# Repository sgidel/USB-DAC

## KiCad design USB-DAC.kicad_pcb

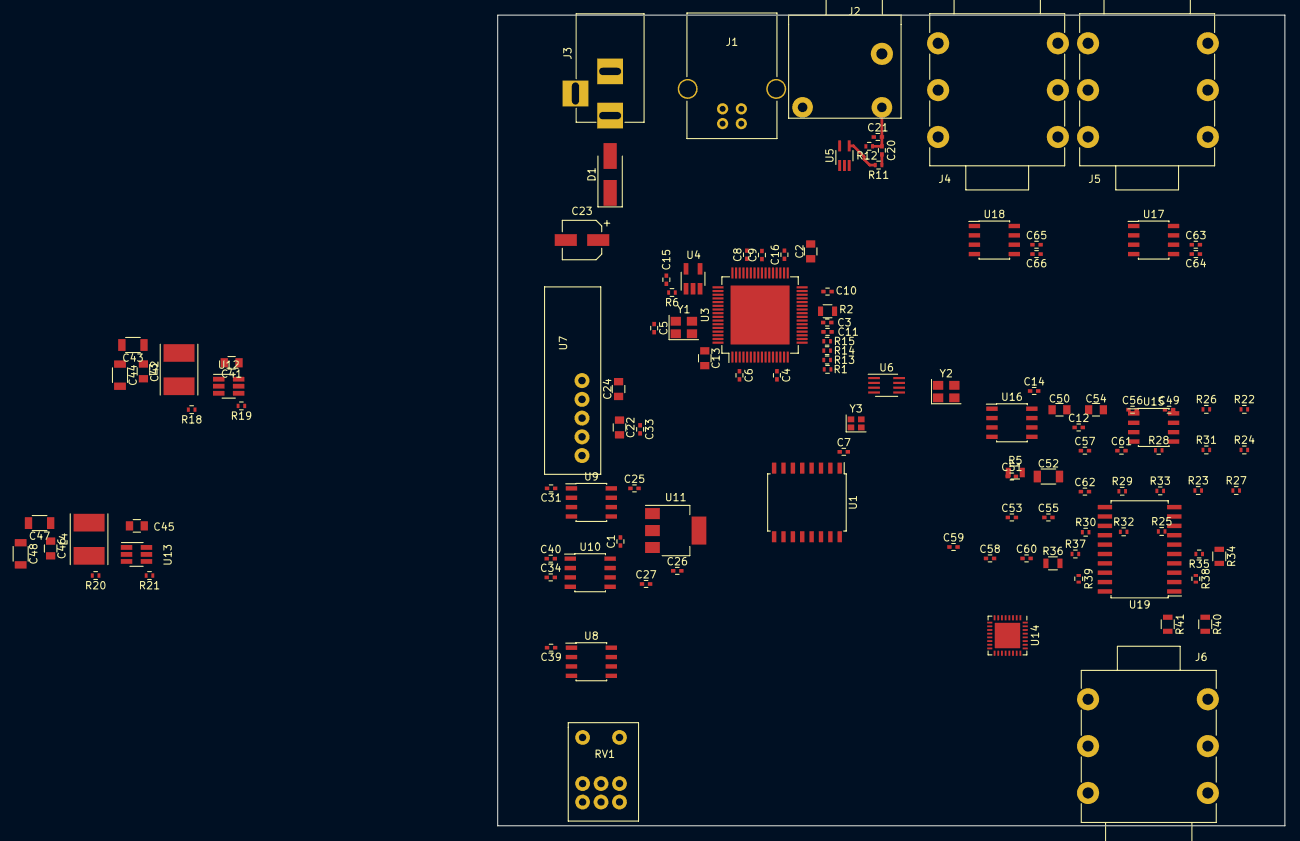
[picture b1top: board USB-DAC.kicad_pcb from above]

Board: 2 copper layers, 106.7 x 109.9 mm, 119 parts (0 on the bottom side), 75 nets.

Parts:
C1, C3, C4, C5, C6, C7, C8, C9, C10, C11, C12, C14, C15, C16, C20, C25, C26, C27, C31, C33, C34, C39, C40, C49, C51, C53, C63, C64, C65, C66: 100n; C_0402
C2, C13, C50: 10u; C_0805
C21: 100p; C_0402
C22, C24: 22u; C_0805
C23: 1000u; CP_Elec_5x5.7
C41, C42, C45, C46: 100n; C_0805
C43, C44, C47, C48: 47u; C_1206
C52: 10u; C_1206
C54: 1u; C_0805
C55, C56: 3n9; C_0402
C57, C58, C59, C60: 470p; C_0402
C61, C62: 22p; C_0402
D1: SK34ATR; D_SMA_Handsoldering
J1: USB_B
J2: SPDIF OUT; pjras1x1s_series
J3: BARREL_JACK
J4, J5, J6: Audio-Jack-3_3Switches; NMJ6HCD2
L3, L4: 2u2; L_Taiyo-Yuden_NR-50xx_HandSoldering
R1, R13, R14, R15: 0; R_0402
R2: 43.2; R_0805
R5: 4.7; R_0805
R6, R35, R37, R38, R39: 1K; R_0402
R11, R12: 220; R_0402
R18: 33K2; R_0402
R19: 10K2; R_0402
R20: 3K74; R_0402
R21: 10K; R_0402
R22, R23, R24, R25: 3K9; R_0402
R26, R27, R32, R33: 4K7; R_0402
R28, R29, R30, R31: 150; R_0402
R34, R36: 51; R_0805
R40, R41: 39.2; R_0805
RV1: P10K; PTR90
U1: ISO7340FC; SOIC-16W_7.5x10.3mm_Pitch1.27mm
U3: XHRA-2HPA; TQFP-64-1EP_10x10mm_Pitch0.5mm
U4: NCP303LSN09T1G; SOT-23-5_HandSoldering
U5: 74LVC1G79; SOT-353_SC-70-5_Handsoldering
U6: TC7WH157; SSOP-8_2.95x2.8mm_Pitch0.65mm
U7: CHINADCDC; chinadcdc
U8: LM78L12_SO8; SOIC-8_3.9x4.9mm_Pitch1.27mm
U9: L78L05_SO8; SOIC-8_3.9x4.9mm_Pitch1.27mm
U10: L79L12_SO8; SOIC-8_3.9x4.9mm_Pitch1.27mm
U11: AP1117-33; SOT-223-3_TabPin2
U12, U13: TPS563209; SOT-23-6_Handsoldering
U14: AK4452; QFN-32-1EP_5x5mm_Pitch0.5mm
U15, U16: NE5534; SOIC-8_3.9x4.9mm_Pitch1.27mm
U17, U18: DRV135; SOIC-8_3.9x4.9mm_Pitch1.27mm
U19: TPA6120A2; SOIC-20W_7.5x12.8mm_Pitch1.27mm
Y1: 24; Crystal_SMD_3225-4pin_3.2x2.5mm
Y2: 24.576; Crystal_SMD_3225-4pin_3.2x2.5mm
Y3: 22.5792; Crystal_SMD_2016-4pin_2.0x1.6mm

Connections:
+1V0: C9.1, C10.1, C11.1, C12.1, C13.1, C46.1, C47.1, C48.1, L4.2, R5.2, R20.2, U3.9, U3.10, U3.20, U3.27, U3.31, U3.39, U3.40, U3.41, U3.52, U3.56, U3.59, U4.2
+3.3VA: C27.1, C49.1, C50.1, U1.10, U1.16, U11.2, U14.11, U14.12, U14.13, U14.28, U14.29
+3V3: C1.1, C2.1, C3.1, C4.1, C5.1, C6.1, C7.1, C8.1, C16.1, C23.1, C25.1, C26.1, C42.1, C43.1, C44.1, D1.1, L3.2, R1.2, R6.2, R13.2, R14.2, R15.2, R18.2, U1.1, U3.3, U3.13, U3.22, U3.34, U3.44, U3.55, U5.5, U6.8, U7.1, U9.8, U11.3, U13.5, Y1.4, Y2.4, Y3.4
+5V: C31.1, C51.1, C52.1, C53.1, U9.1, U14.17, U14.21
+12V: C39.1, C63.1, C65.1, U8.1, U15.7, U16.7, U17.6, U18.6, U19.3, U19.18
-12V: C40.2, C64.2, C66.2, U10.1, U15.4, U16.4, U17.5, U18.5, U19.1, U19.20
/AK4452DAC/DIN: U1.12, U14.4
/AK4452DAC/LRCK: U1.13, U14.3
/AK4452DAC/MCLK: U1.14, U14.1
/AK4452DAC/OUTL: C59.1, R32.2, RV1.3, U15.6
/AK4452DAC/OUTR: C60.1, R33.2, RV1.6, U16.6
/Balanced Out/INL: R36.1, RV1.2, U17.4
/Balanced Out/INR: R34.1, RV1.5, U18.4
/USB/BCLK: U1.11, U14.2
/USB/CSEL: U3.38, U6.6
/USB/D+: J1.3, U3.25
/USB/D-: J1.2, U3.26
/USB/MCLK_INT: U1.3, U3.64, U5.2, U6.5
/USB/SPDIF: U3.42, U5.1
/USB/~RST: R6.1, U3.57, U4.1
GND: C1.2, C2.2, C3.2, C4.2, C5.2, C6.2, C7.2, C8.2, C9.2, C10.2, C11.2, C12.2, C13.2, C14.2, C15.2, C16.2, C21.1, C22.2, C23.2, C24.1, C25.2, C26.2, C27.2, C31.2, C33.2, C34.1, C39.2, C40.1, C42.2, C43.2, C44.2, C46.2, C47.2, C48.2, C49.2, C50.2, C51.2, C52.2, C53.2, C54.1, C57.2, C58.2, C63.2, C64.1, C65.2, C66.1, J1.4, J1.5, J2.2, J3.2, J3.3, J4.3, J4.6, J5.3, J5.6, J6.2, J6.5, R2.2, R12.1, R19.1, R21.1, R26.2, R27.2, R35.1, R37.1, RV1.1, RV1.4, U1.2, U1.8, U1.9, U1.15, U3.54, U3.65, U4.3, U5.3, U6.7, U7.2, U7.4, U8.2, U8.3, U8.6, U8.7, U9.2, U9.3, U9.6, U9.7, U10.5, U11.1, U12.1, U13.1, U14.5, U14.8, U14.9, U14.10, U14.16, U14.20, U14.22, U14.23, U14.24, U14.26, U14.27, U14.30, U17.3, U18.3, Y1.2, Y2.2, Y3.2
unnamed: C14.1, R5.1, U3.53
unnamed: C15.1, U4.5
unnamed: C20.1, C21.2, J2.1, R12.2
unnamed: C20.2, R11.1
unnamed: C22.1, C33.1, U7.3, U8.8
unnamed: C24.2, C34.2, U7.5, U10.2, U10.3, U10.6, U10.7
unnamed: C41.1, U12.6
unnamed: C41.2, L3.1, U12.2
unnamed: C45.1, U13.6
unnamed: C45.2, L4.1, U13.2
unnamed: C54.2, U14.31
unnamed: C55.1, R22.1, R26.1, R28.1
unnamed: C55.2, R23.1, R29.1, R32.1
unnamed: C56.1, R25.1, R27.1, R31.1
unnamed: C56.2, R24.1, R30.1, R33.1
unnamed: C57.1, R28.2, U15.3
unnamed: C58.1, R31.2, U16.3
unnamed: C59.2, R29.2, U15.2
unnamed: C60.2, R30.2, U16.2
unnamed: C61.1, U15.5
unnamed: C61.2, U15.8
unnamed: C62.1, U16.5
unnamed: C62.2, U16.8
unnamed: D1.2, J3.1
unnamed: J4.4, U18.1, U18.2
unnamed: J4.5, U18.7, U18.8
unnamed: J5.4, U17.1, U17.2
unnamed: J5.5, U17.7, U17.8
unnamed: J6.1, R41.2
unnamed: J6.3, R40.2
unnamed: R1.1, U3.15
unnamed: R2.1, U3.24
unnamed: R11.2, U5.4
unnamed: R13.1, U3.17
unnamed: R14.1, U3.18
unnamed: R15.1, U3.19
unnamed: R18.1, R19.2, U12.4
unnamed: R20.1, R21.2, U13.4
unnamed: R23.2, U14.15
unnamed: R24.2, U14.18
unnamed: R25.2, U14.19
unnamed: R34.2, U19.4
unnamed: R35.2, R38.1, U19.5
unnamed: R36.2, U19.17
unnamed: R37.2, R39.1, U19.16
unnamed: R38.2, R40.1, U19.2
unnamed: R39.2, R41.1, U19.19
unnamed: U1.4, U3.1
unnamed: U1.5, U3.2
unnamed: U1.6, U3.4
unnamed: U3.58, Y1.3
unnamed: U6.1, Y2.3
unnamed: U6.2, Y3.3
VBUS: J1.1, U3.23, U12.3, U12.5, U13.3

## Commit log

2017-11-29 Initial Schematics
2017-12-19 Updated schematics and part number fields
2018-01-26 Began PCB layout
2018-01-30 Fixed gitignore issue which leaves out the component cache
2018-01-31 updated to new kicad format
2018-02-11 started routing PCB
